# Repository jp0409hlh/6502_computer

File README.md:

# JP6502 computer

Warning: This repo is still early in development

## Hardware
**Warning** : This section is still under development, do not expect anything to work.
This folder contains the schematics and pcb files for this project.
### main_computer
This folder constains the schematics and pcb files for the JP6502 motherboard.
### others
Future plans : Floppy disk controller expansion card, SD card interface expansion card, ESP32 network expansion card.

## Software
**Warning** : This section is still under development, do not expect anything to work.
This folder contains softwares I wrote for this computer, mainly the OS.

## Credits

+ [Ben eater](http://www.youtube.com/@BenEater) - for the 6502 Youtube series
+ [krallja](http://www.youtube.com/@krallja) - for the [tutorial](https://www.youtube.com/watch?v=0QleiL-WdyM) of interfacing the Tms9918
+ [Doctor Volt](http://www.youtube.com/@DoctorVolt) - for the [tutorial](https://www.youtube.com/watch?v=smgGB_CsXns) of how to connect the Tms9918 to an Arduino, which helped me test my chip
+ [tomcircuit](https://hackaday.io/hacker/1679-tomcircuit) - for the [design](https://hackaday.io/project/160851-tms9918-vdp-with-sram-video-memory) of tms9918 SRAM replacement 
+ [mike's software blog](https://mike42.me/blog/) - for the inspiration of the code for xmodem
+ [sillycowvalley](https://github.com/sillycowvalley) - for the inspiration the [kernel](https://github.com/sillycowvalley/Hopper) 
+ [r/beneater community](https://www.reddit.com/r/beneater/)

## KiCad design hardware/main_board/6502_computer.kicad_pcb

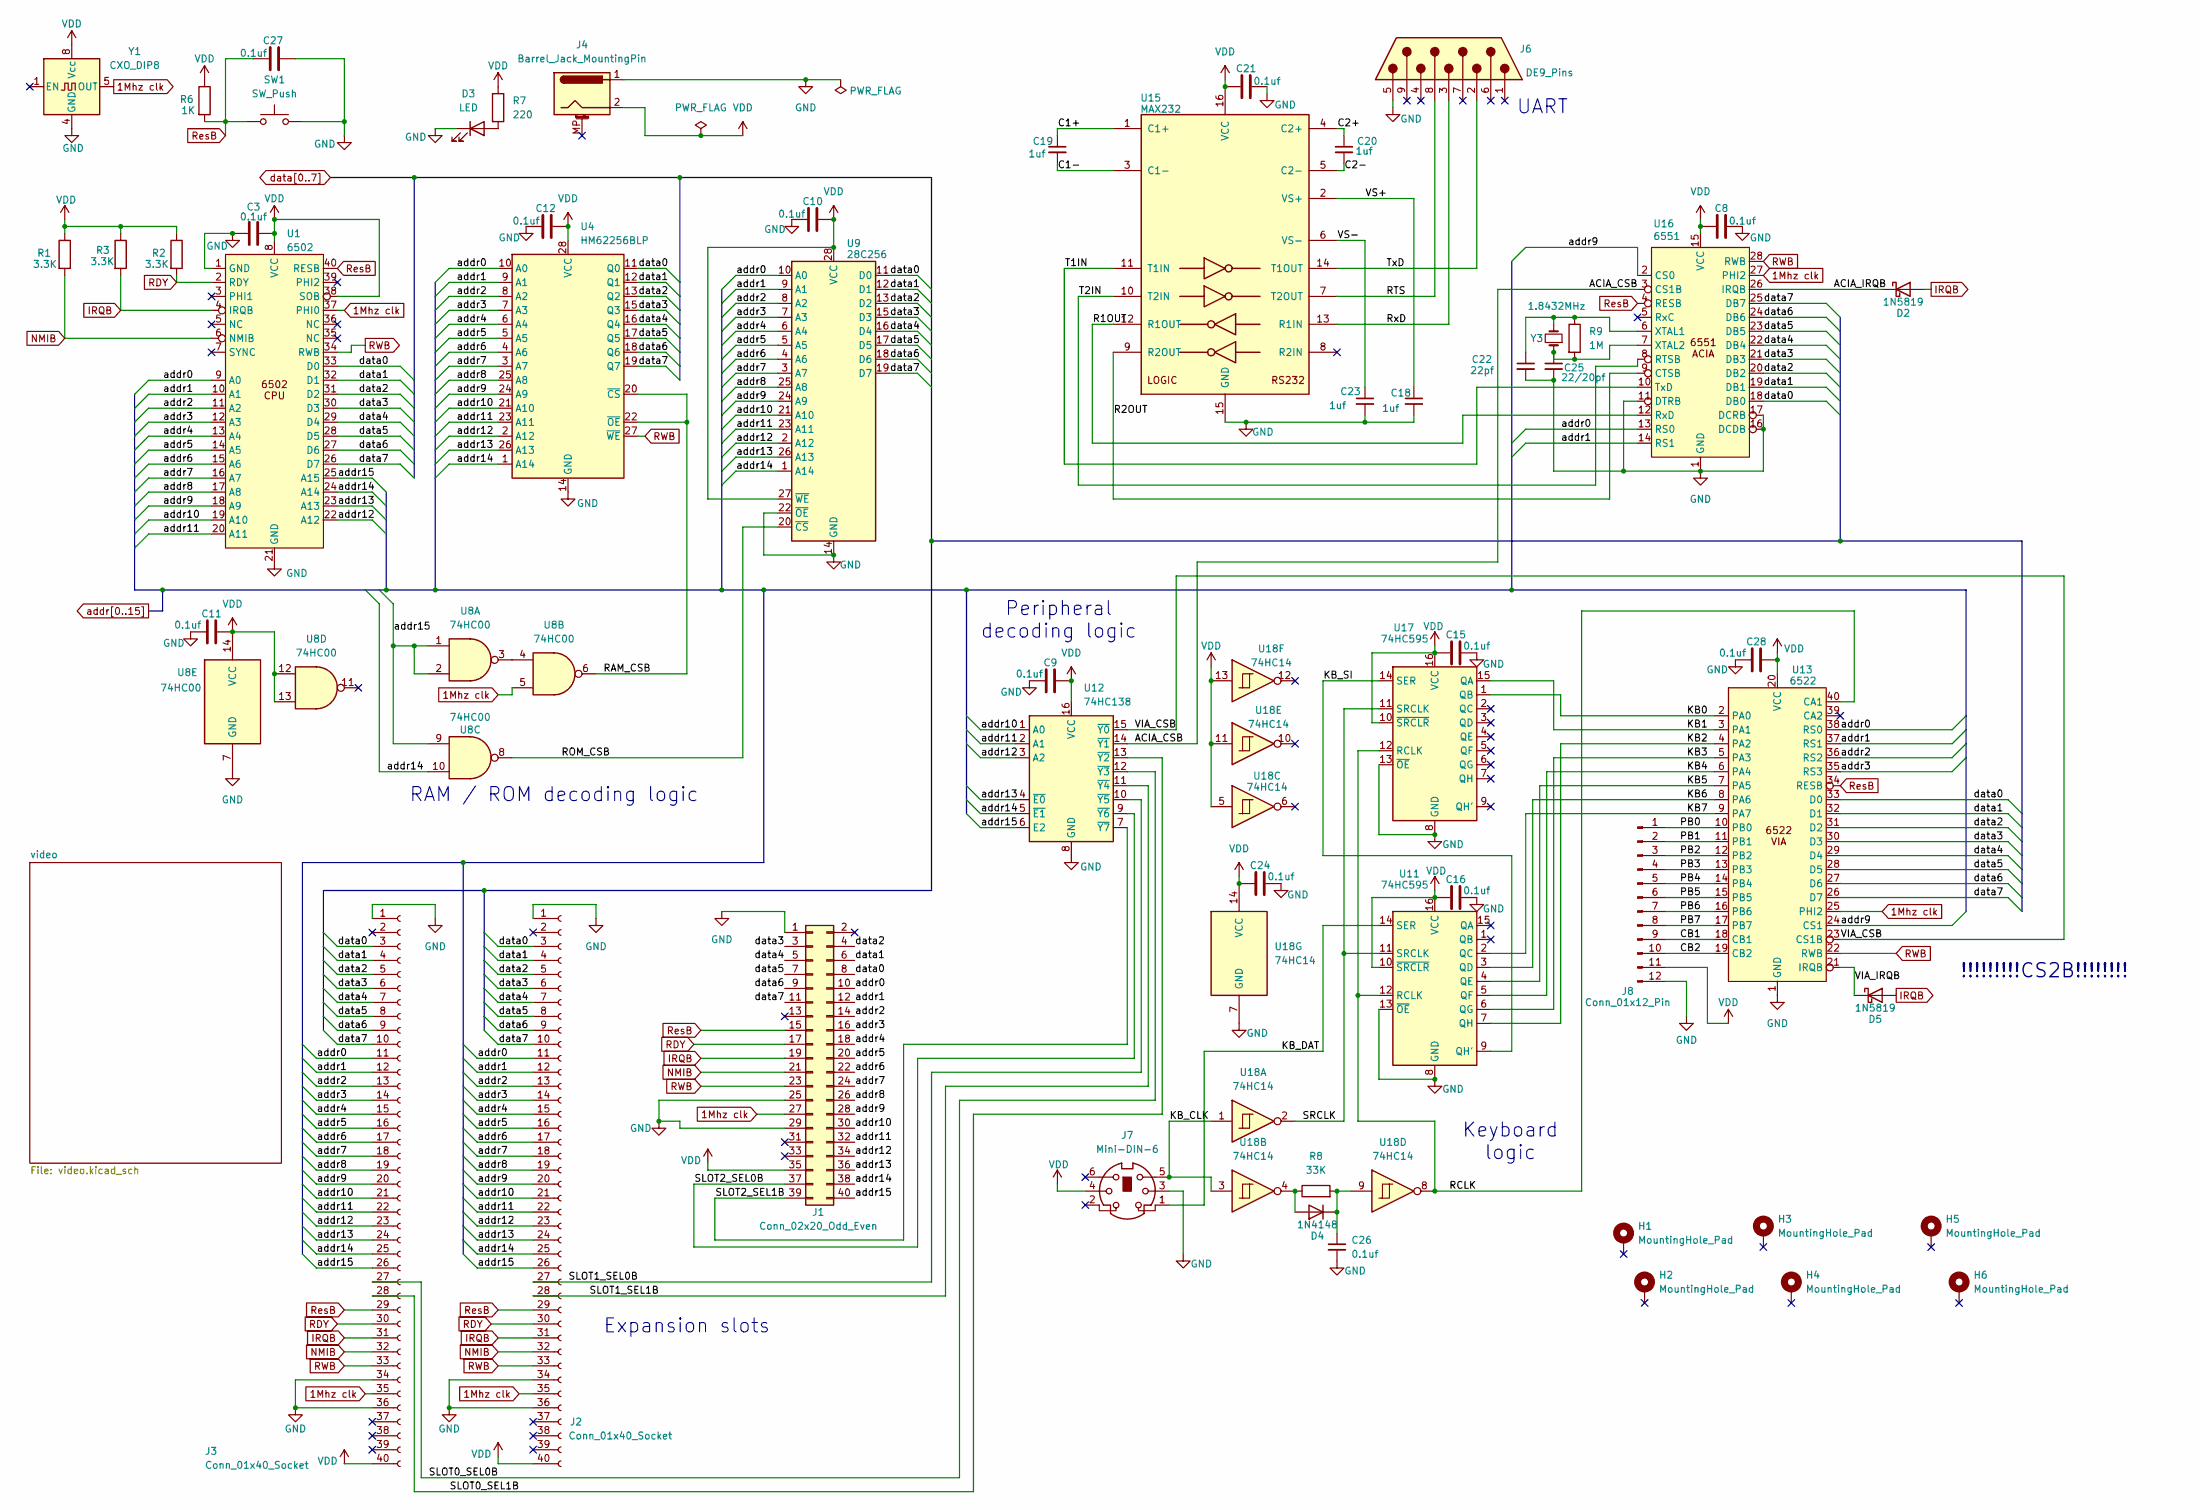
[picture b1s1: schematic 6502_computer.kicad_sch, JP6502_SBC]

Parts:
C3, C8, C9, C10, C11, C12, C15, C16, C21, C24, C26, C27, C28: 0.1uf; C_Disc_D5.0mm_W2.5mm_P2.50mm
C18, C19, C20, C23: 1uf; C_Disc_D5.1mm_W3.2mm_P5.00mm
C22: 22pf; C_Disc_D5.0mm_W2.5mm_P2.50mm
C25: 22/20pf; C_Disc_D5.0mm_W2.5mm_P2.50mm
D2, D5: 1N5819; D_DO-41_SOD81_P10.16mm_Horizontal
D3: LED; LED_D3.0mm
D4: 1N4148; D_DO-35_SOD27_P7.62mm_Horizontal
H1, H2, H3, H4, H5, H6: MountingHole_Pad; MountingHole_3.2mm_M3_ISO7380_Pad
J1: Conn_02x20_Odd_Even; IDC-Header_2x20_P2.54mm_Vertical
J2, J3: Conn_01x40_Socket; PinSocket_1x40_P2.54mm_Vertical
J4: Barrel_Jack_MountingPin; BarrelJack_Horizontal
J6: DE9_Pins; DSUB-9_Socket_Horizontal_P2.77x2.84mm_EdgePinOffset7.70mm_H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
J7: Mini-DIN-6; TE_5749180-1
J8: Conn_01x12_Pin; PinHeader_1x12_P2.54mm_Horizontal
R1, R2, R3: 3.3K; R_Axial_DIN0207_L6.3mm_D2.5mm_P10.16mm_Horizontal
R6: 1K; R_Axial_DIN0207_L6.3mm_D2.5mm_P10.16mm_Horizontal
R7: 220; R_Axial_DIN0207_L6.3mm_D2.5mm_P10.16mm_Horizontal
R8: 33K; R_Axial_DIN0207_L6.3mm_D2.5mm_P10.16mm_Horizontal
R9: 1M; R_Axial_DIN0207_L6.3mm_D2.5mm_P10.16mm_Horizontal
SW1: SW_Push; SW_PUSH_6mm_H8mm
U1: 6502; DIP-40_W15.24mm_Socket_LongPads
U4: HM62256BLP; DIP-28_W15.24mm_Socket_LongPads
U8: 74HC00; DIP-14_W7.62mm_Socket_LongPads
U9: 28C256; DIP_Socket-28_W11.9_W12.7_W15.24_W17.78_W18.5_3M_228-1277-0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
U11, U17: 74HC595; DIP-16_W7.62mm_Socket_LongPads
U12: 74HC138; DIP-16_W7.62mm_Socket_LongPads
U13: 6522; DIP-40_W15.24mm_Socket_LongPads
U15: MAX232; DIP-16_W7.62mm_Socket_LongPads
U16: 6551; DIP-28_W15.24mm_Socket_LongPads
U18: 74HC14; DIP-14_W7.62mm_Socket_LongPads
Y1: CXO_DIP8; Oscillator_DIP-8
Y3: 1.8432MHz; Crystal_HC18-U_Vertical

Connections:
1Mhz clk: J1.27, J2.35, J3.35, U1.37 (PHI0), U8.5, U13.25 (PHI2), U16.27 (PHI2), Y1.5 (OUT)
/ACIA_CSB: U12.14 (~Y1), U16.3 (CS1B)
/ACIA_IRQB: D2.1 (K), U16.26 (IRQB)
/C1+: C19.1, U15.1 (C1+)
/C1-: C19.2, U15.3 (C1-)
/C2+: C20.1, U15.4 (C2+)
/C2-: C20.2, U15.5 (C2-)
/CB1: J8.9, U13.18 (CB1)
/CB2: J8.10, U13.19 (CB2)
/KB0: U13.2 (PA0), U17.1 (QB)
/KB1: U13.3 (PA1), U17.15 (QA)
/KB2: U11.7 (QH), U13.4 (PA2)
/KB3: U11.6 (QG), U13.5 (PA3)
/KB4: U11.5 (QF), U13.6 (PA4)
/KB5: U11.4 (QE), U13.7 (PA5)
/KB6: U11.3 (QD), U13.8 (PA6)
/KB7: U11.2 (QC), U13.9 (PA7)
/KB_CLK: J7.5, U18.1, U18.3
/KB_DAT: J7.1, U11.14 (SER)
/KB_SI: U11.9 (QH'), U17.14 (SER)
/PB0: J8.1, U13.10 (PB0)
/PB1: J8.2, U13.11 (PB1)
/PB2: J8.3, U13.12 (PB2)
/PB3: J8.4, U13.13 (PB3)
/PB4: J8.5, U13.14 (PB4)
/PB5: J8.6, U13.15 (PB5)
/PB6: J8.7, U13.16 (PB6)
/PB7: J8.8, U13.17 (PB7)
/R1OUT: U15.12 (R1OUT), U16.12 (RxD)
/R2OUT: U15.9 (R2OUT), U16.9 (CTSB)
/RAM_CSB: U4.20 (~CS), U4.22 (~OE), U8.6
/RCLK: U11.12 (RCLK), U13.40 (CA1), U17.12 (RCLK), U18.8
/ROM_CSB: U8.8, U9.20 (~CS)
/RTS: J6.8, U15.7 (T2OUT)
/RxD: J6.3, U15.13 (R1IN)
/SLOT0_SEL0B: J3.27, U12.12 (~Y3)
/SLOT0_SEL1B: J3.28, U12.13 (~Y2)
/SLOT1_SEL0B: J2.27, U12.10 (~Y5)
/SLOT1_SEL1B: J2.28, U12.11 (~Y4)
/SLOT2_SEL0B: J1.37, U12.9 (~Y6)
/SLOT2_SEL1B: J1.39, U12.7 (~Y7)
/SRCLK: U11.11 (SRCLK), U17.11 (SRCLK), U18.2
/T1IN: U15.11 (T1IN), U16.10 (TxD)
/T2IN: U15.10 (T2IN), U16.8 (RTSB)
/TxD: J6.2, U15.14 (T1OUT)
/VIA_CSB: U12.15 (~Y0), U13.23 (CS1B)
/VIA_IRQB: D5.1 (K), U13.21 (IRQB)
/VS+: C18.1, U15.2 (VS+)
/VS-: C23.1, U15.6 (VS-)
GND: C3.1, C8.2, C9.1, C10.1, C11.1, C12.1, C15.2, C16.2, C18.2, C21.2, C22.2, C23.2, C24.2, C25.2, C26.2, C27.2, C28.1, D3.1 (K), J1.1, J1.25, J1.29, J2.1, J2.34, J2.36, J3.1, J3.34, J3.36, J4.1, J6.5, J7.3, J8.12, SW1.2, U1.1 (GND), U1.21 (GND), U4.14 (GND), U8.7 (GND), U9.14 (GND), U9.22 (~OE), U11.8 (GND), U11.13 (~OE), U12.8 (GND), U13.1 (GND), U15.15 (GND), U16.1 (GND), U16.11 (DTRB), U16.16 (DCDB), U16.17 (DCRB), U17.8 (GND), U17.13 (~OE), U18.7 (GND), Y1.4 (GND); also elsewhere on the board
IRQB: D2.2 (A), D5.2 (A), J1.19, J2.31, J3.31, R3.2, U1.4 (IRQB); also elsewhere on the board
NMIB: J1.21, J2.32, J3.32, R1.2, U1.6 (NMIB)
unnamed: D3.2 (A), R7.2
unnamed: D4.2 (A), R8.1, U18.4
unnamed: C26.1, D4.1 (K), R8.2, U18.9
unnamed: U8.3, U8.4
unnamed: C22.1, R9.1, U16.6 (XTAL1), Y3.2
unnamed: C25.1, R9.2, U16.7 (XTAL2), Y3.1
RDY: J1.17, J2.30, J3.30, R2.2, U1.2 (RDY)
RWB: J1.23, J2.33, J3.33, U1.34 (RWB), U4.27 (~WE), U13.22 (RWB), U16.28 (RWB); also elsewhere on the board
ResB: C27.1, J1.15, J2.29, J3.29, R6.2, SW1.1, U1.40 (RESB), U13.34 (RESB), U16.4 (RESB); also elsewhere on the board
VDD: C3.2, C8.1, C9.2, C10.2, C11.2, C12.2, C15.1, C16.1, C21.1, C24.1, C28.2, J1.35, J2.40, J3.40, J4.2, J7.4, J8.11, R1.1, R2.1, R3.1, R6.1, R7.1, U1.8 (VCC), U1.38 (SOB), U4.28 (VCC), U8.12, U8.13, U8.14 (VCC), U9.27 (~WE), U9.28 (VCC), U11.10 (~SRCLR), U11.16 (VCC), U12.16 (VCC), U13.20 (VCC), U15.16 (VCC), U16.15 (VCC), U17.10 (~SRCLR), U17.16 (VCC), U18.5, U18.11, U18.13, U18.14 (VCC), Y1.8 (Vcc); also elsewhere on the board
addr0: J1.10, J2.11, J3.11, U1.9 (A0), U4.10 (A0), U9.10 (A0), U13.38 (RS0), U16.13 (RS0); also elsewhere on the board
addr1: J1.12, J2.12, J3.12, U1.10 (A1), U4.9 (A1), U9.9 (A1), U13.37 (RS1), U16.14 (RS1)
addr2: J1.14, J2.13, J3.13, U1.11 (A2), U4.8 (A2), U9.8 (A2), U13.36 (RS2)
addr3: J1.16, J2.14, J3.14, U1.12 (A3), U4.7 (A3), U9.7 (A3), U13.35 (RS3)
addr4: J1.18, J2.15, J3.15, U1.13 (A4), U4.6 (A4), U9.6 (A4)
addr5: J1.20, J2.16, J3.16, U1.14 (A5), U4.5 (A5), U9.5 (A5)
addr6: J1.22, J2.17, J3.17, U1.15 (A6), U4.4 (A6), U9.4 (A6)
addr7: J1.24, J2.18, J3.18, U1.16 (A7), U4.3 (A7), U9.3 (A7)
addr8: J1.26, J2.19, J3.19, U1.17 (A8), U4.25 (A8), U9.25 (A8)
addr9: J1.28, J2.20, J3.20, U1.18 (A9), U4.24 (A9), U9.24 (A9), U13.24 (CS1), U16.2 (CS0)
addr10: J1.30, J2.21, J3.21, U1.19 (A10), U4.21 (A10), U9.21 (A10), U12.1 (A0)
addr11: J1.32, J2.22, J3.22, U1.20 (A11), U4.23 (A11), U9.23 (A11), U12.2 (A1); also elsewhere on the board
addr12: J1.34, J2.23, J3.23, U1.22 (A12), U4.2 (A12), U9.2 (A12), U12.3 (A2); also elsewhere on the board
addr13: J1.36, J2.24, J3.24, U1.23 (A13), U4.26 (A13), U9.26 (A13), U12.4 (~E0); also elsewhere on the board
addr14: J1.38, J2.25, J3.25, U1.24 (A14), U4.1 (A14), U8.10, U9.1 (A14), U12.5 (~E1); also elsewhere on the board
addr15: J1.40, J2.26, J3.26, U1.25 (A15), U8.1, U8.2, U8.9, U12.6 (E2); also elsewhere on the board
data0: J1.8, J2.3, J3.3, U1.33 (D0), U4.11 (Q0), U9.11 (D0), U13.33 (D0), U16.18 (DB0); also elsewhere on the board
data1: J1.6, J2.4, J3.4, U1.32 (D1), U4.12 (Q1), U9.12 (D1), U13.32 (D1), U16.19 (DB1); also elsewhere on the board
data2: J1.4, J2.5, J3.5, U1.31 (D2), U4.13 (Q2), U9.13 (D2), U13.31 (D2), U16.20 (DB2); also elsewhere on the board
data3: J1.3, J2.6, J3.6, U1.30 (D3), U4.15 (Q3), U9.15 (D3), U13.30 (D3), U16.21 (DB3); also elsewhere on the board
data4: J1.5, J2.7, J3.7, U1.29 (D4), U4.16 (Q4), U9.16 (D4), U13.29 (D4), U16.22 (DB4); also elsewhere on the board
data5: J1.7, J2.8, J3.8, U1.28 (D5), U4.17 (Q5), U9.17 (D5), U13.28 (D5), U16.23 (DB5); also elsewhere on the board
data6: J1.9, J2.9, J3.9, U1.27 (D6), U4.18 (Q6), U9.18 (D6), U13.27 (D6), U16.24 (DB6); also elsewhere on the board
data7: J1.11, J2.10, J3.10, U1.26 (D7), U4.19 (Q7), U9.19 (D7), U13.26 (D7), U16.25 (DB7); also elsewhere on the board

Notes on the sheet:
!!!!!!!!!CS2B!!!!!!!!
UART
RAM / ROM decoding logic
Expansion slots
Keyboard logic
Peripheral decoding logic

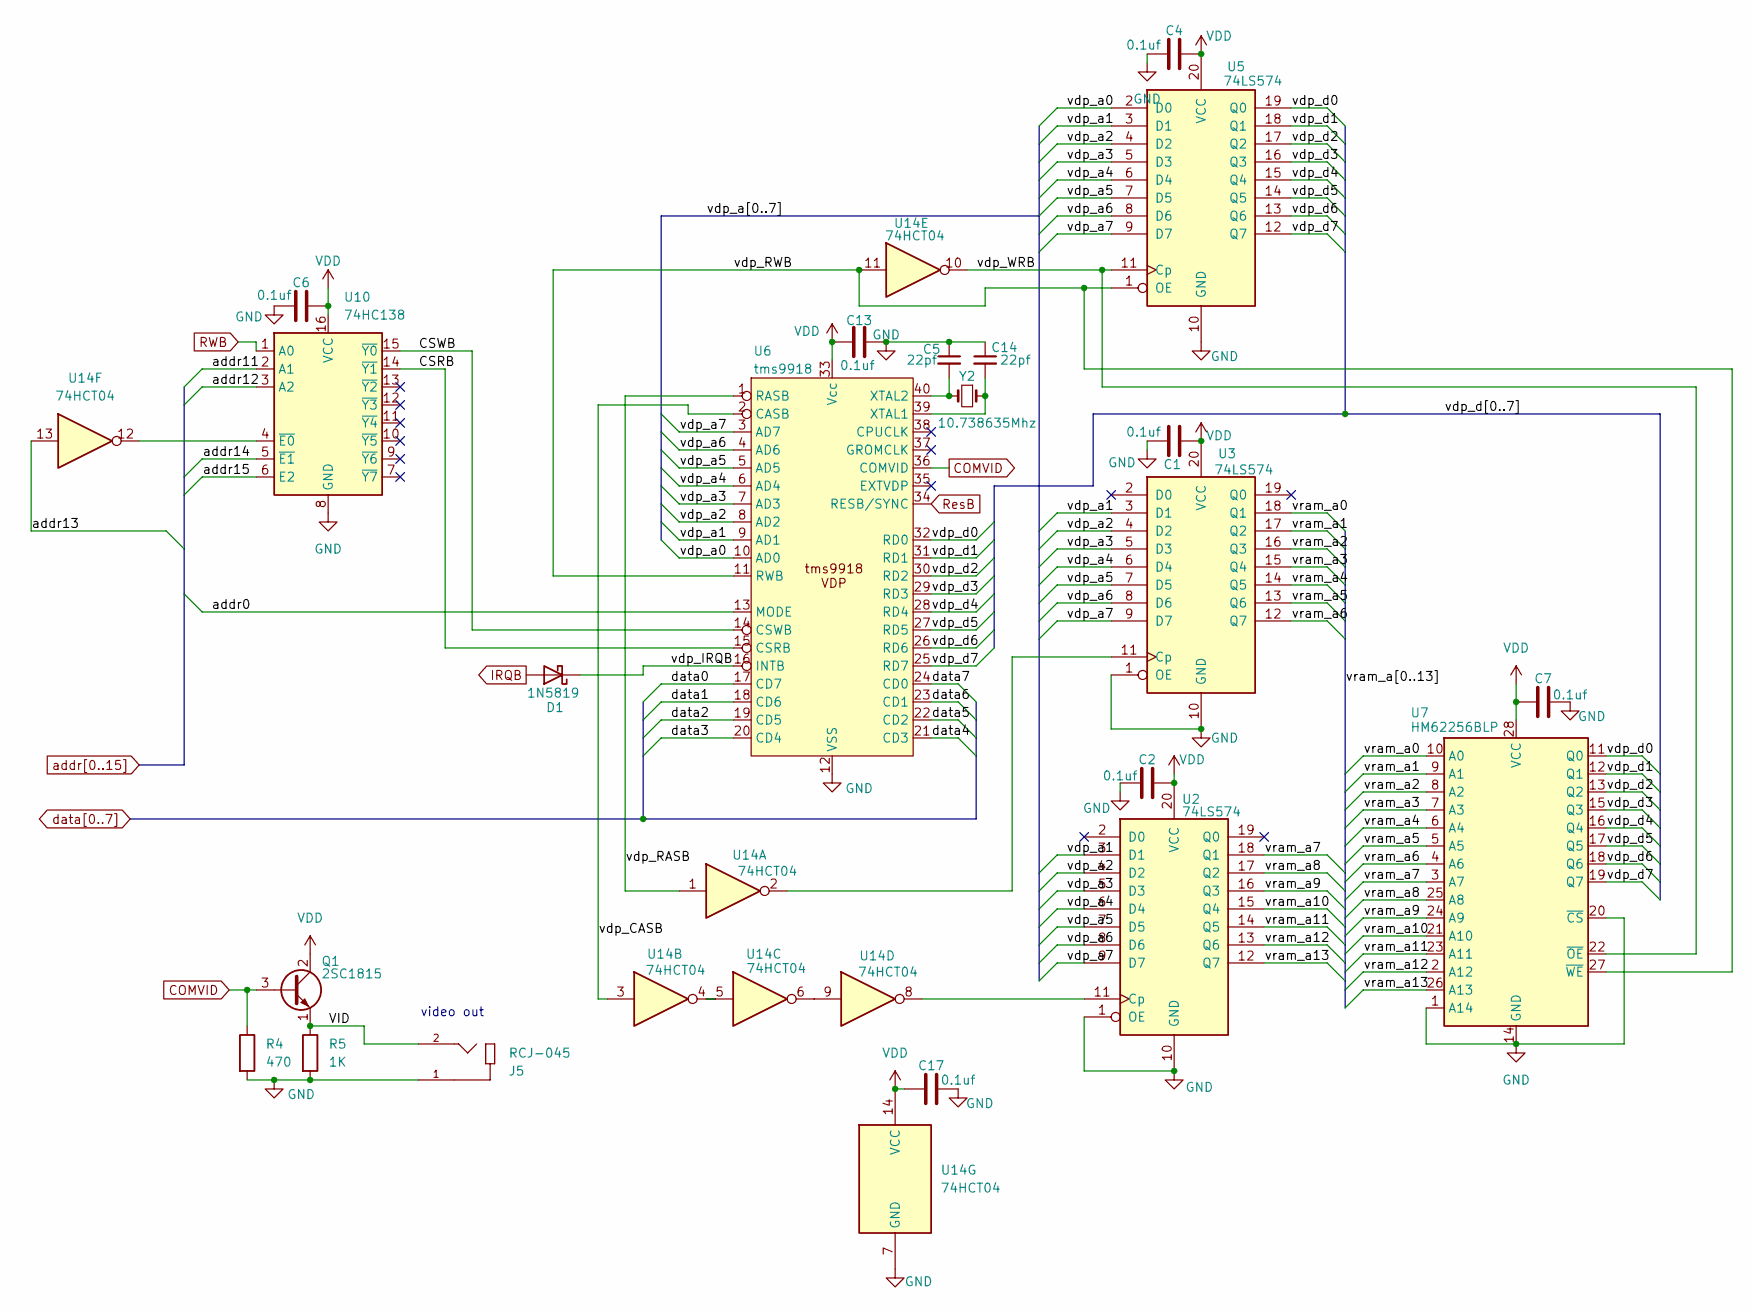
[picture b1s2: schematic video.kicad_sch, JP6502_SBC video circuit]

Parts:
C1, C2, C4, C6, C7, C13, C17: 0.1uf; C_Disc_D5.0mm_W2.5mm_P2.50mm
C5, C14: 22pf; C_Disc_D5.0mm_W2.5mm_P2.50mm
D1: 1N5819; D_DO-41_SOD81_P10.16mm_Horizontal
J5: RCJ-045; CUI_RCJ-045
Q1: 2SC1815; TO-92_HandSolder
R4: 470; R_Axial_DIN0207_L6.3mm_D2.5mm_P10.16mm_Horizontal
R5: 1K; R_Axial_DIN0207_L6.3mm_D2.5mm_P10.16mm_Horizontal
U2, U3, U5: 74LS574; DIP-20_W7.62mm_Socket_LongPads
U6: tms9918; DIP-40_W15.24mm_Socket_LongPads
U7: HM62256BLP; DIP-28_W15.24mm_LongPads
U10: 74HC138; DIP-16_W7.62mm_Socket_LongPads
U14: 74HCT04; DIP-14_W7.62mm_Socket_LongPads
Y2: 10.738635Mhz; Crystal_HC18-U_Vertical

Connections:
/video/CSRB: U6.15 (CSRB), U10.14 (~Y1)
/video/CSWB: U6.14 (CSWB), U10.15 (~Y0)
/video/VID: J5.2, Q1.1 (E), R5.1
/video/vdp_CASB: U6.2 (CASB), U14.3
/video/vdp_IRQB: D1.1 (K), U6.16 (INTB)
/video/vdp_RASB: U6.1 (RASB), U14.1
/video/vdp_RWB: U5.1 (OE), U6.11 (RWB), U7.27 (~WE), U14.11
/video/vdp_WRB: U5.11 (Cp), U7.22 (~OE), U14.10
/video/vdp_a0: U5.2 (D0), U6.10 (AD0)
/video/vdp_a1: U2.3 (D1), U3.3 (D1), U5.3 (D1), U6.9 (AD1)
/video/vdp_a2: U2.4 (D2), U3.4 (D2), U5.4 (D2), U6.8 (AD2)
/video/vdp_a3: U2.5 (D3), U3.5 (D3), U5.5 (D3), U6.7 (AD3)
/video/vdp_a4: U2.6 (D4), U3.6 (D4), U5.6 (D4), U6.6 (AD4)
/video/vdp_a5: U2.7 (D5), U3.7 (D5), U5.7 (D5), U6.5 (AD5)
/video/vdp_a6: U2.8 (D6), U3.8 (D6), U5.8 (D6), U6.4 (AD6)
/video/vdp_a7: U2.9 (D7), U3.9 (D7), U5.9 (D7), U6.3 (AD7)
/video/vdp_d0: U5.19 (Q0), U6.32 (RD0), U7.11 (Q0)
/video/vdp_d1: U5.18 (Q1), U6.31 (RD1), U7.12 (Q1)
/video/vdp_d2: U5.17 (Q2), U6.30 (RD2), U7.13 (Q2)
/video/vdp_d3: U5.16 (Q3), U6.29 (RD3), U7.15 (Q3)
/video/vdp_d4: U5.15 (Q4), U6.28 (RD4), U7.16 (Q4)
/video/vdp_d5: U5.14 (Q5), U6.27 (RD5), U7.17 (Q5)
/video/vdp_d6: U5.13 (Q6), U6.26 (RD6), U7.18 (Q6)
/video/vdp_d7: U5.12 (Q7), U6.25 (RD7), U7.19 (Q7)
/video/vram_a0: U3.18 (Q1), U7.10 (A0)
/video/vram_a1: U3.17 (Q2), U7.9 (A1)
/video/vram_a2: U3.16 (Q3), U7.8 (A2)
/video/vram_a3: U3.15 (Q4), U7.7 (A3)
/video/vram_a4: U3.14 (Q5), U7.6 (A4)
/video/vram_a5: U3.13 (Q6), U7.5 (A5)
/video/vram_a6: U3.12 (Q7), U7.4 (A6)
/video/vram_a7: U2.18 (Q1), U7.3 (A7)
/video/vram_a8: U2.17 (Q2), U7.25 (A8)
/video/vram_a9: U2.16 (Q3), U7.24 (A9)
/video/vram_a10: U2.15 (Q4), U7.21 (A10)
/video/vram_a11: U2.14 (Q5), U7.23 (A11)
/video/vram_a12: U2.13 (Q6), U7.2 (A12)
/video/vram_a13: U2.12 (Q7), U7.26 (A13)
COMVID: Q1.3 (B), R4.1, U6.36 (COMVID)
GND: C1.1, C2.1, C4.1, C5.1, C6.1, C7.2, C13.2, C14.1, C17.2, J5.1, R4.2, R5.2, U2.1 (OE), U2.10 (GND), U3.1 (OE), U3.10 (GND), U5.10 (GND), U6.12 (VSS), U7.1 (A14), U7.14 (GND), U7.20 (~CS), U10.8 (GND), U14.7 (GND); also elsewhere on the board
IRQB: D1.2 (A); also elsewhere on the board
unnamed: U2.11 (Cp), U14.8
unnamed: U3.11 (Cp), U14.2
unnamed: C14.2, U6.39 (XTAL1), Y2.1
unnamed: C5.2, U6.40 (XTAL2), Y2.2
unnamed: U10.4 (~E0), U14.12
unnamed: U14.4, U14.5
unnamed: U14.6, U14.9
RWB: U10.1 (A0); also elsewhere on the board
ResB: U6.34 (RESB/SYNC); also elsewhere on the board
VDD: C1.2, C2.2, C4.2, C6.2, C7.1, C13.1, C17.1, Q1.2 (C), U2.20 (VCC), U3.20 (VCC), U5.20 (VCC), U6.33 (Vcc), U7.28 (VCC), U10.16 (VCC), U14.14 (VCC); also elsewhere on the board
addr0: U6.13 (MODE); also elsewhere on the board
addr11: U10.2 (A1); also elsewhere on the board
addr12: U10.3 (A2); also elsewhere on the board
addr13: U14.13; also elsewhere on the board
addr14: U10.5 (~E1); also elsewhere on the board
addr15: U10.6 (E2); also elsewhere on the board
data0: U6.17 (CD7); also elsewhere on the board
data1: U6.18 (CD6); also elsewhere on the board
data2: U6.19 (CD5); also elsewhere on the board
data3: U6.20 (CD4); also elsewhere on the board
data4: U6.21 (CD3); also elsewhere on the board
data5: U6.22 (CD2); also elsewhere on the board
data6: U6.23 (CD1); also elsewhere on the board
data7: U6.24 (CD0); also elsewhere on the board

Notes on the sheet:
video out

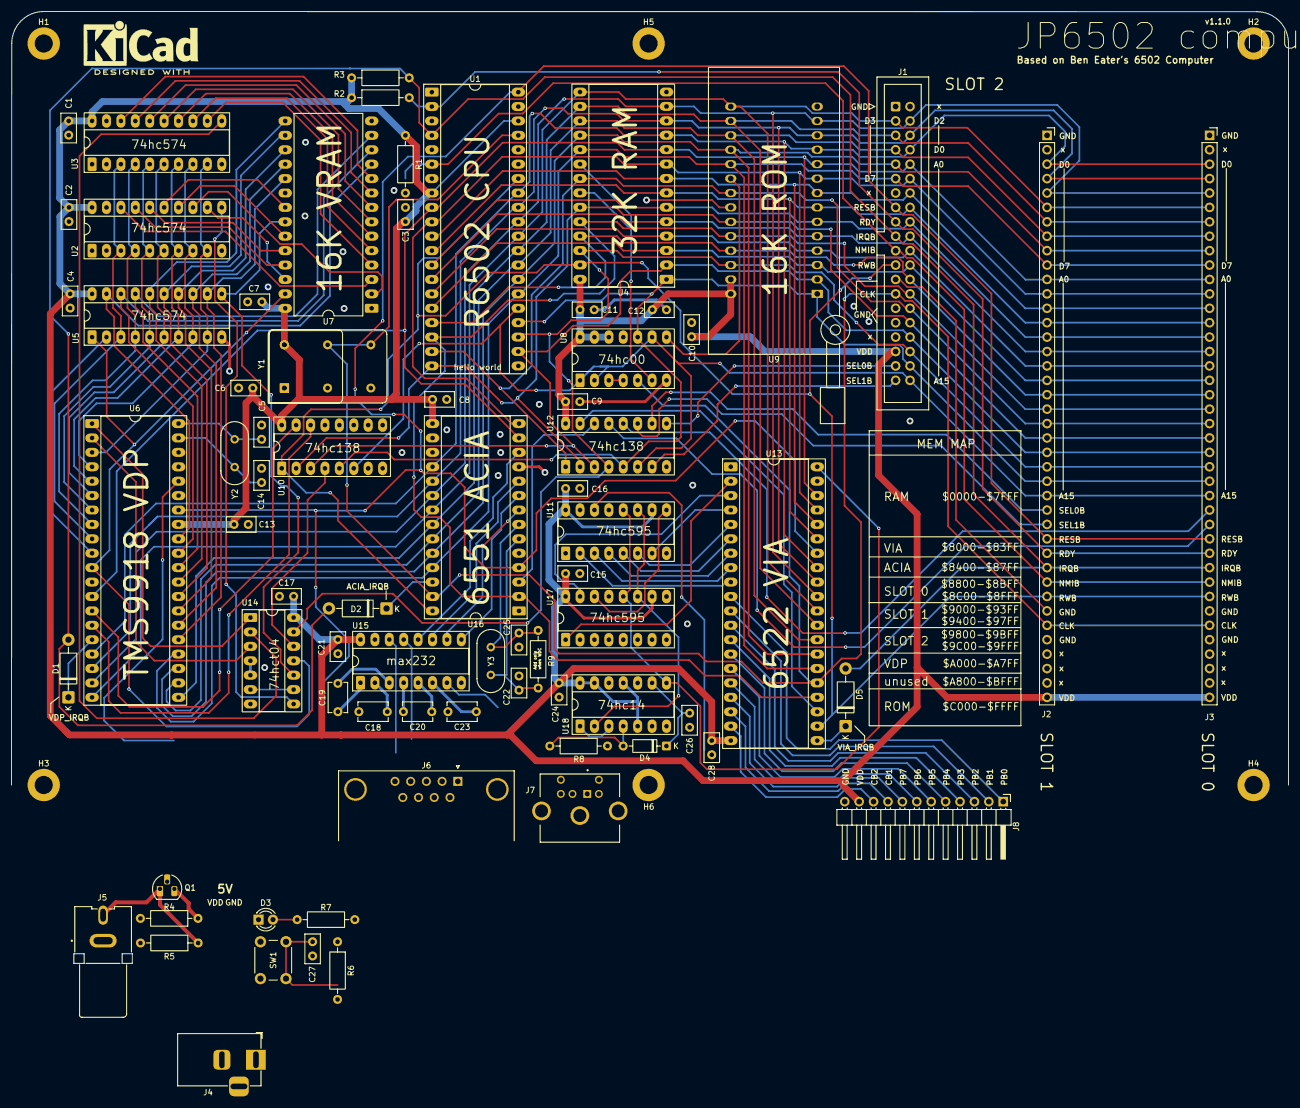
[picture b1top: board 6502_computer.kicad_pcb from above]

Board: 2 copper layers, 225.1 x 167.8 mm, 80 parts (0 on the bottom side), 132 nets.

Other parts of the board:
kicad_logo: KiCad-Logo2_8mm_SilkScreen

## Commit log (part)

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2026-05-21 Updated gitignore
2026-05-21 Generated gerber fill and pdf schematics
2026-05-22 Updated readme credits
2026-05-24 updated pcb and sch
